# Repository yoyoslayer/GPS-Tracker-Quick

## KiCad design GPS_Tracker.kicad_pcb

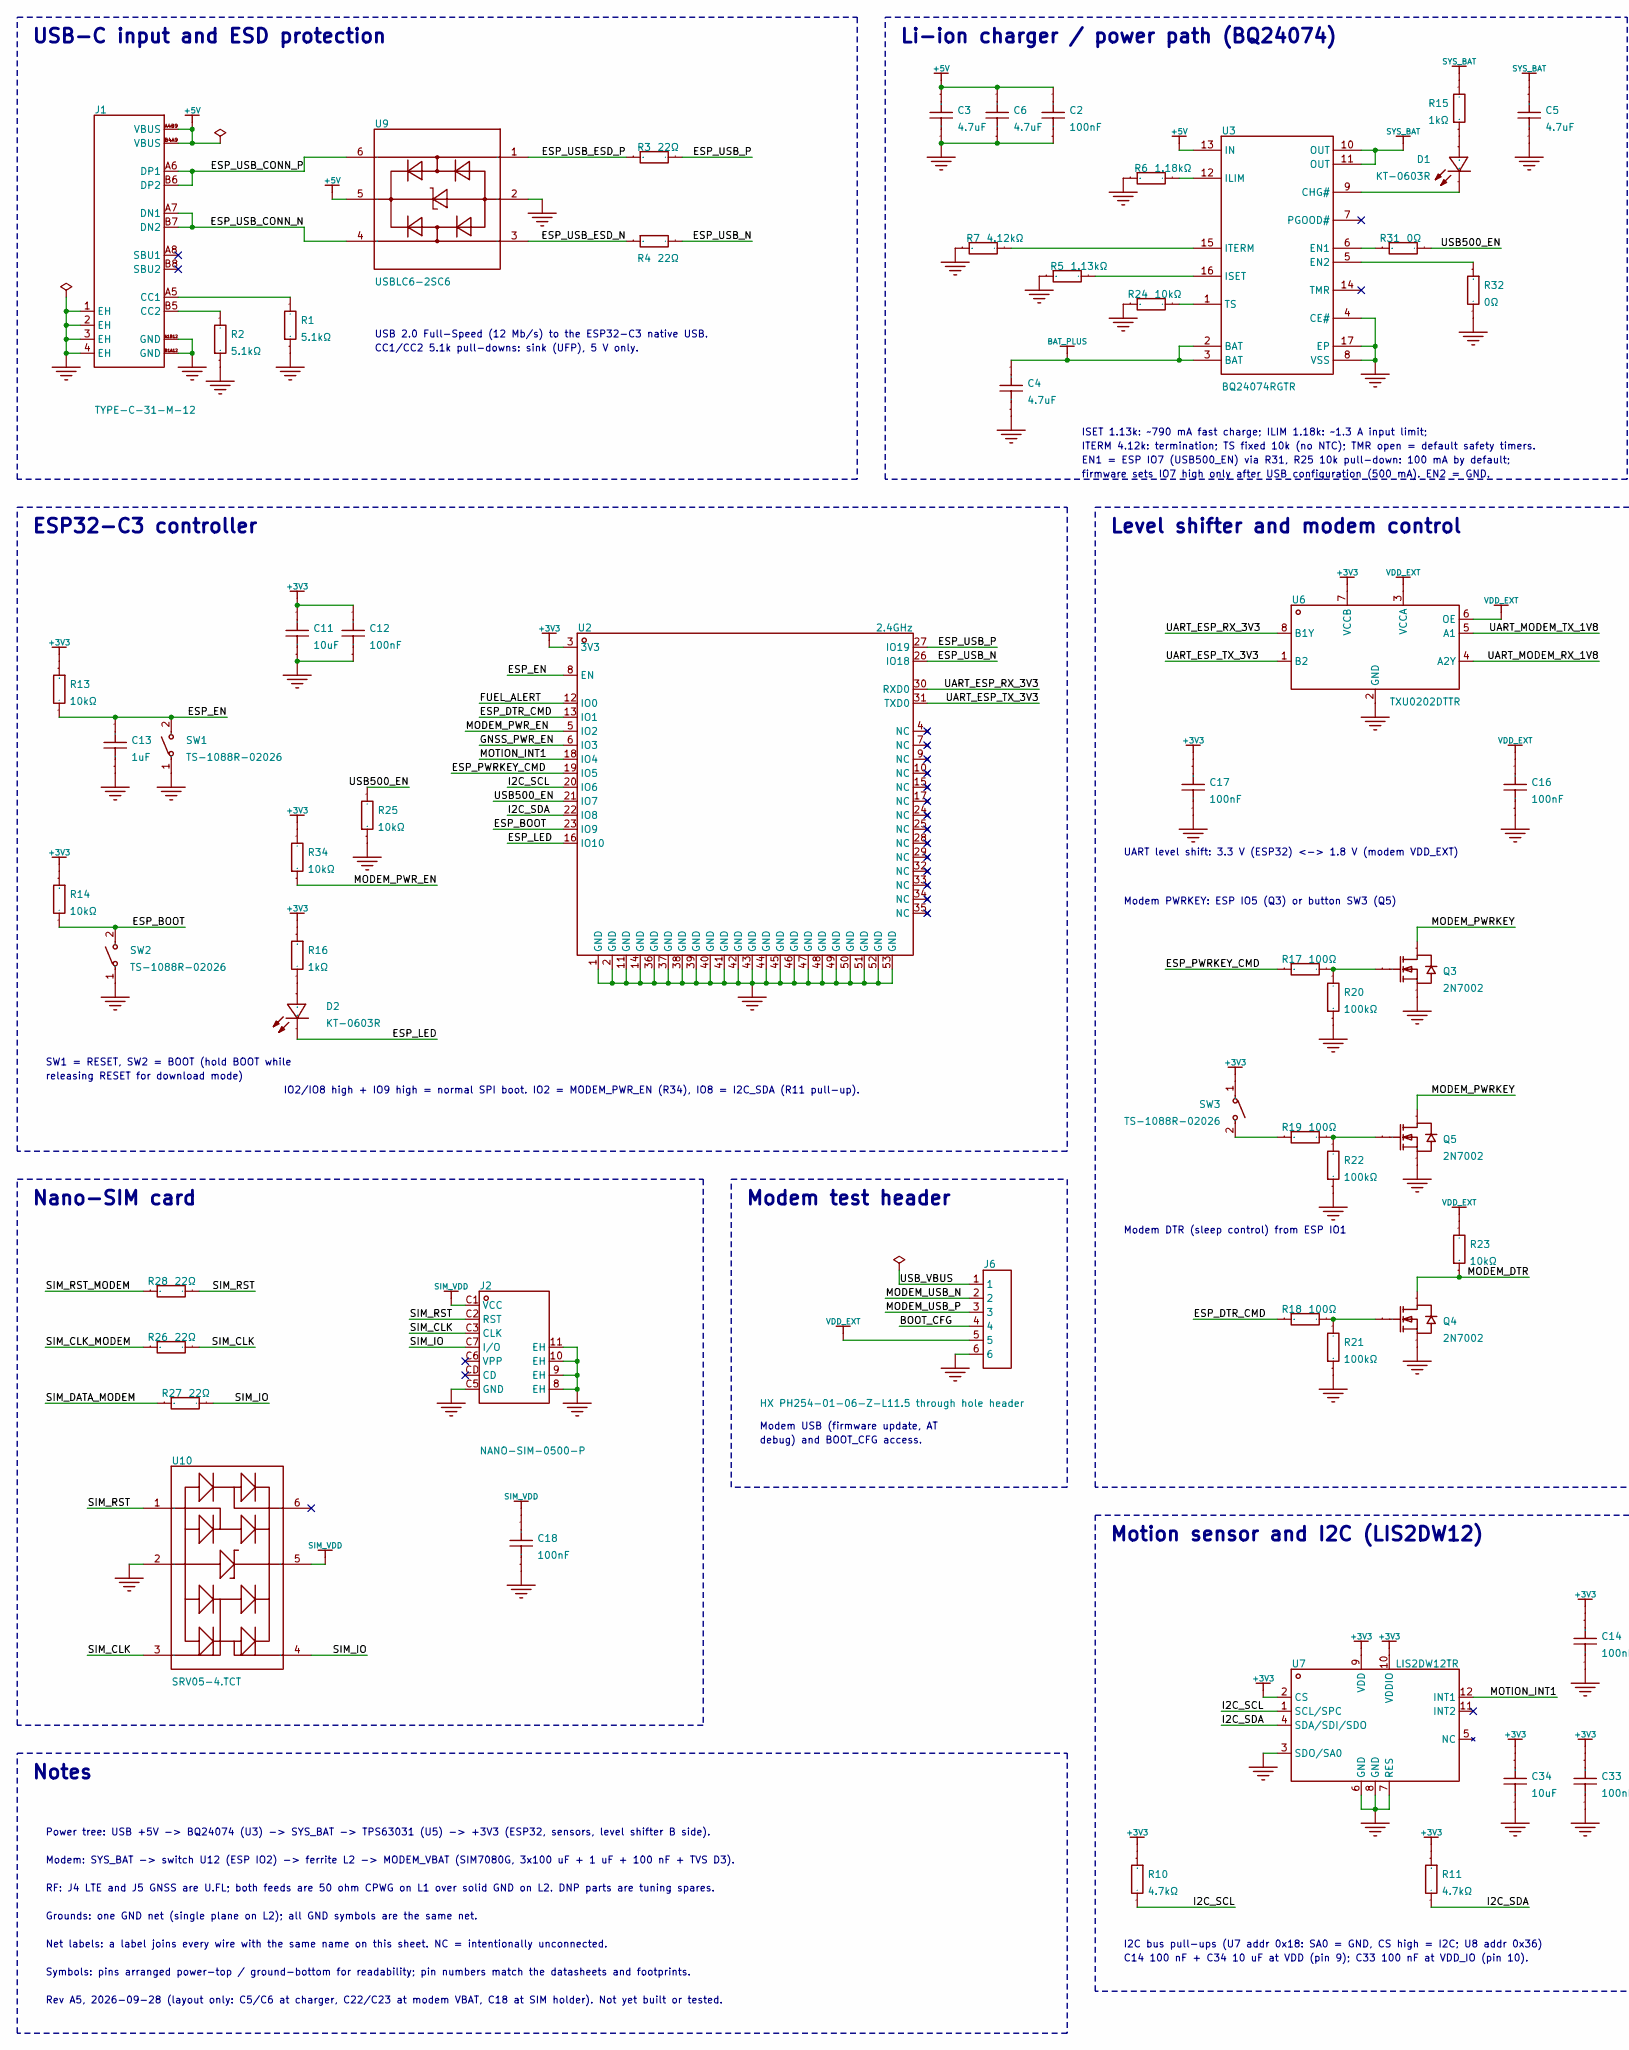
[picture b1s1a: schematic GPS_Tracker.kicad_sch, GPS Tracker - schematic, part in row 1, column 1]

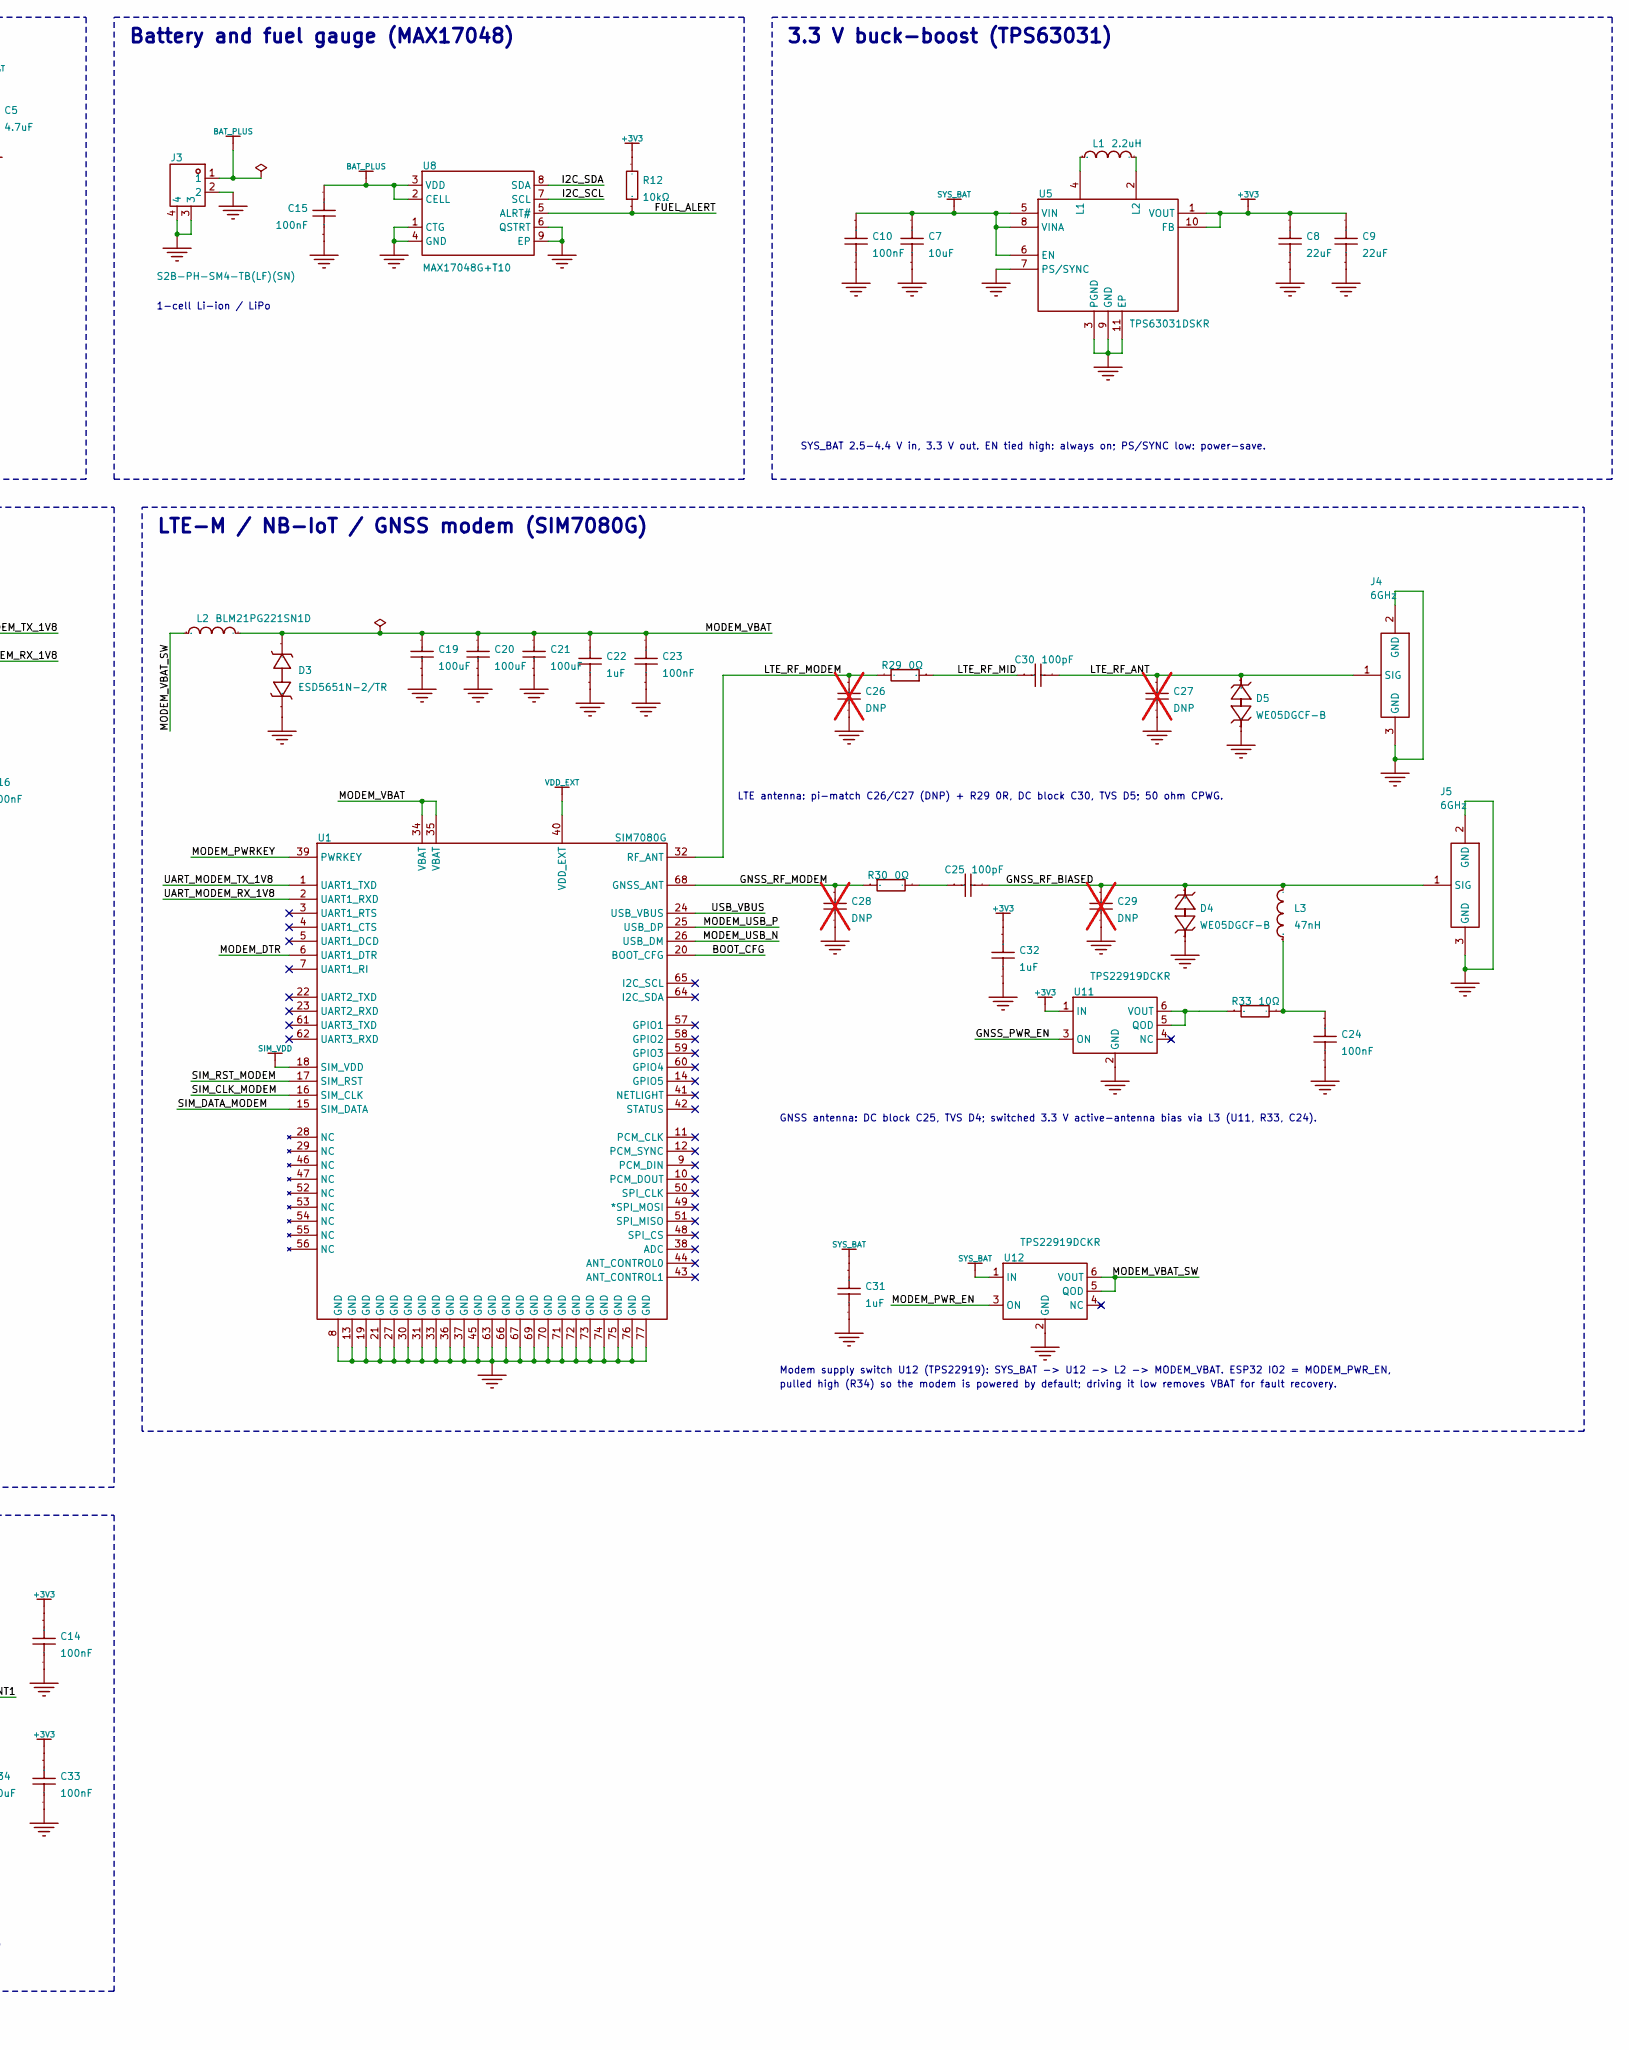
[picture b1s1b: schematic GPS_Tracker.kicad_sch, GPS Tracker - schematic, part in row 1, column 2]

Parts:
C2: 100nF; C2_C_0603_1608Metric; Manufacturer Part CC0603KRX7R9BB104; LCSC Part Name 100nF ±10% 50V
C3: 4.7uF; C3_C_0603_1608Metric; Manufacturer Part CL10A475KO8NNNC; LCSC Part Name 4.7uF ±10% 16V
C4: 4.7uF; C4_C_0603_1608Metric; Manufacturer Part CL10A475KO8NNNC; LCSC Part Name 4.7uF ±10% 16V
C5: 4.7uF; C5_C_0603_1608Metric; Manufacturer Part CL10A475KO8NNNC; LCSC Part Name 4.7uF ±10% 16V
C6: 4.7uF; C6_C_0603_1608Metric; Manufacturer Part CL10A475KO8NNNC; LCSC Part Name 4.7uF ±10% 16V
C7: 10uF; C7_C_0805_2012Metric; Manufacturer Part CL21A106KAYNNNE; LCSC Part Name 10uF ±10% 25V
C8: 22uF; C8_C_0805_2012Metric; Manufacturer Part CL21A226MAQNNNE; LCSC Part Name 22uF ±20% 25V
C9: 22uF; C9_C_0805_2012Metric; Manufacturer Part CL21A226MAQNNNE; LCSC Part Name 22uF ±20% 25V
C10: 100nF; C10_C_0603_1608Metric; Manufacturer Part CC0603KRX7R9BB104; LCSC Part Name 100nF ±10% 50V
C11: 10uF; C11_C_0805_2012Metric; Manufacturer Part CL21A106KAYNNNE; LCSC Part Name 10uF ±10% 25V
C12: 100nF; C12_C_0603_1608Metric; Manufacturer Part CC0603KRX7R9BB104; LCSC Part Name 100nF ±10% 50V
C13: 1uF; C13_C_0603_1608Metric; Manufacturer Part CL10A105KB8NNNC; LCSC Part Name 1uF ±10% 50V
C14: 100nF; C14_C_0603_1608Metric; Manufacturer Part CC0603KRX7R9BB104; LCSC Part Name 100nF ±10% 50V
C15: 100nF; C15_C_0603_1608Metric; Manufacturer Part CC0603KRX7R9BB104; LCSC Part Name 100nF ±10% 50V
C16: 100nF; C16_C_0603_1608Metric; Manufacturer Part CC0603KRX7R9BB104; LCSC Part Name 100nF ±10% 50V
C17: 100nF; C17_C_0603_1608Metric; Manufacturer Part CC0603KRX7R9BB104; LCSC Part Name 100nF ±10% 50V
C18: 100nF; C18_C_0603_1608Metric; Manufacturer Part CC0603KRX7R9BB104; LCSC Part Name 100nF ±10% 50V
C19: 100uF; C19_C_1210_3225Metric; Manufacturer Part CL32A107MQVNNNE; LCSC Part Name 100uF ±20% 6.3V
C20: 100uF; C20_C_1210_3225Metric; Manufacturer Part CL32A107MQVNNNE; LCSC Part Name 100uF ±20% 6.3V
C21: 100uF; C21_C_1210_3225Metric; Manufacturer Part CL32A107MQVNNNE; LCSC Part Name 100uF ±20% 6.3V
C22: 1uF; C22_C_0603_1608Metric; Manufacturer Part CL10A105KB8NNNC; LCSC Part Name 1uF ±10% 50V
C23: 100nF; C23_C_0603_1608Metric; Manufacturer Part CC0603KRX7R9BB104; LCSC Part Name 100nF ±10% 50V
C24: 100nF; C24_C_0603_1608Metric; Manufacturer Part CC0603KRX7R9BB104; LCSC Part Name 100nF ±10% 50V
C25, C30: 100pF; C25_C_0402_1005Metric; Manufacturer Part CL05C101JB5NNNC; LCSC Part Name 100pF ±5% 50V
C26, C27, C28, C29: DNP; C25_C_0402_1005Metric; Manufacturer Part CL05C101JB5NNNC; LCSC Part Name 100pF ±5% 50V; not fitted
C31: 1uF; C31_C_0603_1608Metric; Manufacturer Part CL10A105KB8NNNC; LCSC Part Name 1uF ±10% 50V
C32: 1uF; C32_C_0603_1608Metric; Manufacturer Part CL10A105KB8NNNC; LCSC Part Name 1uF ±10% 50V
C33: 100nF; C33_C_0603_1608Metric; Manufacturer Part CC0603KRX7R9BB104; LCSC Part Name 100nF ±10% 50V
C34: 10uF; C34_C_0805_2012Metric; Manufacturer Part CL21A106KAYNNNE; LCSC Part Name 10uF ±10% 25V
D1: KT-0603R; D1_LED_0603_1608Metric; Manufacturer Part KT-0603R; LCSC Part Name 0603 红灯 高亮
D2: KT-0603R; D2_LED_0603_1608Metric; Manufacturer Part KT-0603R; LCSC Part Name 0603 红灯 高亮
D3: ESD5651N-2/TR; D3_D_SOD-882; Manufacturer Part ESD5651N-2/TR; LCSC Part Name 双向TVS 4.5V截止 峰值脉冲电流：35A@8/20us
D4, D5: WE05DGCF-B; D4_D_SOD-882; Manufacturer Part WE05DGCF-B; LCSC Part Name 瞬态电压抑制器
J1: TYPE-C-31-M-12; J1_USB_C_Receptacle_HRO_TYPE-C-31-M-12_trimmed; Manufacturer Part TYPE-C-31-M-12; LCSC Part Name Type-C 母 卧贴
J2: NANO-SIM-0500-P; Zhongdi_NANO-SIM-0500-P; Manufacturer Part NANO-SIM-0500-P; LCSC Part Name 自弹式 NanoSIM卡 卡座
J3: S2B-PH-SM4-TB(LF)(SN); J3_JST_PH_S2B-PH-SM4-TB_1x02-1MP_P2.00mm_Horizontal_trimmed; Manufacturer Part S2B-PH-SM4-TB(LF)(SN); LCSC Part Name 1x2P 间距:2mm 卧贴 系列:PH
J4: 6GHz; J4_U.FL_Hirose_U.FL-R-SMT-1_Vertical; Manufacturer Part U.FL-R-SMT-1(80); LCSC Part Name IPEX 内针
J5: 6GHz; J5_U.FL_Hirose_U.FL-R-SMT-1_Vertical; Manufacturer Part U.FL-R-SMT-1(80); LCSC Part Name IPEX 内针
J6: HX PH254-01-06-Z-L11.5 through hole header; J6_PinHeader_1x06_P2.54mm_Vertical; Manufacturer Part HX PH254-01-06-Z-L11.5 through hole hea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; LCSC Part Name 1x6P 间距:2.54mm 方针 直插
L1: 2.2uH; L1_IND-SMD_L3.0-W3.0; Manufacturer Part SWPA3015S2R2MT; LCSC Part Name 2.2uH ±20%
L2: BLM21PG221SN1D; L2_L_0805_2012Metric; Manufacturer Part BLM21PG221SN1D; LCSC Part Name 单路 0805磁珠 阻抗220Ω@100MHz
L3: 47nH; L3_L_0402_1005Metric; Manufacturer Part SDWL1005C47NGSTF; LCSC Part Name 停产 47nH ±2%
Q3: 2N7002; Q3_SOT-23; Manufacturer Part 2N7002; LCSC Part Name 1个N沟道 耐压:60V 电流:115mA
Q4: 2N7002; Q4_SOT-23; Manufacturer Part 2N7002; LCSC Part Name 1个N沟道 耐压:60V 电流:115mA
Q5: 2N7002; Q5_SOT-23; Manufacturer Part 2N7002; LCSC Part Name 1个N沟道 耐压:60V 电流:115mA
R1: 5.1kΩ; R1_R_0603_1608Metric; Manufacturer Part 0603WAF5101T5E; LCSC Part Name 5.1kΩ ±1% 100mW 厚膜电阻
R2: 5.1kΩ; R2_R_0603_1608Metric; Manufacturer Part 0603WAF5101T5E; LCSC Part Name 5.1kΩ ±1% 100mW 厚膜电阻
R3: 22Ω; R3_R_0603_1608Metric; Manufacturer Part 0603WAF220JT5E; LCSC Part Name 22Ω ±1% 100mW 厚膜电阻
R4: 22Ω; R4_R_0603_1608Metric; Manufacturer Part 0603WAF220JT5E; LCSC Part Name 22Ω ±1% 100mW 厚膜电阻
R5: 1.13kΩ; R5_R_0603_1608Metric; Manufacturer Part 0603WAF1131T5E; LCSC Part Name 1.13kΩ ±1% 100mW 厚膜电阻
R6: 1.18kΩ; R6_R_0603_1608Metric; Manufacturer Part 0603WAF1181T5E; LCSC Part Name 1.18kΩ ±1% 100mW 厚膜电阻
R7: 4.12kΩ; R7_R_0603_1608Metric; Manufacturer Part 0603WAF4121T5E; LCSC Part Name 4.12kΩ ±1% 100mW 厚膜电阻
R10: 4.7kΩ; R10_R_0603_1608Metric; Manufacturer Part 0603WAF4701T5E; LCSC Part Name 4.7kΩ ±1% 100mW 厚膜电阻
R11: 4.7kΩ; R11_R_0603_1608Metric; Manufacturer Part 0603WAF4701T5E; LCSC Part Name 4.7kΩ ±1% 100mW 厚膜电阻
R12: 10kΩ; R12_R_0603_1608Metric; Manufacturer Part 0603WAF1002T5E; LCSC Part Name 厚膜电阻 10kΩ ±1% 100mW
R13: 10kΩ; R13_R_0603_1608Metric; Manufacturer Part 0603WAF1002T5E; LCSC Part Name 厚膜电阻 10kΩ ±1% 100mW
R14: 10kΩ; R14_R_0603_1608Metric; Manufacturer Part 0603WAF1002T5E; LCSC Part Name 厚膜电阻 10kΩ ±1% 100mW
R15: 1kΩ; R15_R_0603_1608Metric; Manufacturer Part 0603WAF1001T5E; LCSC Part Name 1kΩ ±1% 100mW 厚膜电阻
R16: 1kΩ; R16_R_0603_1608Metric; Manufacturer Part 0603WAF1001T5E; LCSC Part Name 1kΩ ±1% 100mW 厚膜电阻
R17: 100Ω; R17_R_0603_1608Metric; Manufacturer Part 0603WAF1000T5E; LCSC Part Name 100Ω ±1% 100mW 厚膜电阻
R18: 100Ω; R18_R_0603_1608Metric; Manufacturer Part 0603WAF1000T5E; LCSC Part Name 100Ω ±1% 100mW 厚膜电阻
R19: 100Ω; R19_R_0603_1608Metric; Manufacturer Part 0603WAF1000T5E; LCSC Part Name 100Ω ±1% 100mW 厚膜电阻
R20: 100kΩ; R20_R_0603_1608Metric; Manufacturer Part 0603WAF1003T5E; LCSC Part Name 100kΩ ±1% 100mW 厚膜电阻
R21: 100kΩ; R21_R_0603_1608Metric; Manufacturer Part 0603WAF1003T5E; LCSC Part Name 100kΩ ±1% 100mW 厚膜电阻
R22: 100kΩ; R22_R_0603_1608Metric; Manufacturer Part 0603WAF1003T5E; LCSC Part Name 100kΩ ±1% 100mW 厚膜电阻
R23: 10kΩ; R23_R_0603_1608Metric; Manufacturer Part 0603WAF1002T5E; LCSC Part Name 厚膜电阻 10kΩ ±1% 100mW
R24: 10kΩ; R24_R_0603_1608Metric; Manufacturer Part 0603WAF1002T5E; LCSC Part Name 厚膜电阻 10kΩ ±1% 100mW
R25: 10kΩ; R25_R_0603_1608Metric; Manufacturer Part RC0603FR-0710KL; LCSC Part Name 厚膜电阻 10kΩ ±1% 100mW
R26: 22Ω; R26_R_0603_1608Metric; Manufacturer Part 0603WAF220JT5E; LCSC Part Name 22Ω ±1% 100mW 厚膜电阻
R27: 22Ω; R27_R_0603_1608Metric; Manufacturer Part 0603WAF220JT5E; LCSC Part Name 22Ω ±1% 100mW 厚膜电阻
R28: 22Ω; R28_R_0603_1608Metric; Manufacturer Part 0603WAF220JT5E; LCSC Part Name 22Ω ±1% 100mW 厚膜电阻
R29: 0Ω; R29_R_0402_1005Metric; Manufacturer Part 0402WGF0000TCE; LCSC Part Name 0Ω ±1% 62.5mW 厚膜电阻
R30: 0Ω; R30_R_0402_1005Metric; Manufacturer Part 0402WGF0000TCE; LCSC Part Name 0Ω ±1% 62.5mW 厚膜电阻
R31: 0Ω; R31_R_0603_1608Metric; Manufacturer Part 0603WAF0000T5E; LCSC Part Name 0Ω ±1% 100mW 厚膜电阻
R32: 0Ω; R32_R_0603_1608Metric; Manufacturer Part 0603WAF0000T5E; LCSC Part Name 0Ω ±1% 100mW 厚膜电阻
R33: 10Ω; R33_R_0603_1608Metric; Manufacturer Part RC0603FR-0710RL; LCSC Part Name 厚膜电阻 10Ω ±1% 100mW
R34: 10kΩ; R34_R_0603_1608Metric; Manufacturer Part 0603WAF1002T5E; LCSC Part Name 厚膜电阻 10kΩ ±1% 100mW
SW1: TS-1088R-02026; SW1_SW_Push_1P1T_NO_CK_KMR2; Manufacturer Part TS-1088R-02026; LCSC Part Name 3.9*2.93*2mm 立贴 轻触开关
SW2: TS-1088R-02026; SW2_SW_Push_1P1T_NO_CK_KMR2; Manufacturer Part TS-1088R-02026; LCSC Part Name 3.9*2.93*2mm 立贴 轻触开关
SW3: TS-1088R-02026; SW3_SW_Push_1P1T_NO_CK_KMR2; Manufacturer Part TS-1088R-02026; LCSC Part Name 3.9*2.93*2mm 立贴 轻触开关
U1: SIM7080G; SIMCom_SIM7080G_HD_V1.03; Manufacturer Part SIM7080G; LCSC Part Name 多频段CAT-M和NB-IoT模块
U2: 2.4GHz; U2_ESP32-C3-MINI-1_trimmed; Manufacturer Part ESP32-C3-MINI-1-H4X; LCSC Part Name 不带固件 支持2.4GHz Wi-Fi和蓝牙5的小尺寸模组
U3: BQ24074RGTR; U3_QFN-16-1EP_3x3mm_P0.5mm_EP1.7x1.7mm; Manufacturer Part BQ24074RGTR; LCSC Part Name 1.5A USB友好型锂离子电池充电器和电源路径管理IC
U5: TPS63031DSKR; U5_WSON-10-1EP_2.5x2.5mm_P0.5mm_EP1.2x2mm; Manufacturer Part TPS63031DSKR; LCSC Part Name 升降压型 900mA 1.8V~5.5V
U6: TXU0202DTTR; U6_Texas_X1SON-8_2x1mm_P0.5mm; Manufacturer Part TXU0202DTTR; LCSC Part Name 具有施密特触发输入和三态输出的双位定向电压电平转换器
U7: LIS2DW12TR; U7_LGA-12_2x2mm_P0.5mm; Manufacturer Part LIS2DW12TR; LCSC Part Name 高性能超低功耗3轴加速度计
U8: MAX17048G+T10; U8_TDFN-8-1EP_2x2mm_P0.5mm_EP0.8x1.2mm; Manufacturer Part MAX17048G+T10; LCSC Part Name 3uA单节/双节电池电量计，带ModelGauge算法
U9: USBLC6-2SC6; U9_SOT-23-6; Manufacturer Part USBLC6-2SC6; LCSC Part Name 单向ESD
U10: SRV05-4.TCT; U10_SOT-23-6; Manufacturer Part SRV05-4.TCT; LCSC Part Name SRV05-4.TCT
U11: TPS22919DCKR; U11_SOT-363_SC-70-6; Manufacturer Part TPS22919DCKR; LCSC Part Name 具有受控上升时间的5.5V、1.5A、90mΩ自保护负载开关
U12: TPS22919DCKR; U12_SOT-363_SC-70-6; Manufacturer Part TPS22919DCKR; LCSC Part Name 具有受控上升时间的5.5V、1.5A、90mΩ自保护负载开关

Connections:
+3V3: C8.2, C9.2, C11.2, C12.2, C14.1, C17.1, C32.1, C33.1, C34.1, R10.1, R11.1, R12.2, R13.1, R14.1, R16.1, R34.2, SW3.1, U2.3 (3V3), U5.1 (VOUT), U5.10 (FB), U6.7 (VCCB), U7.2 (CS), U7.9 (VDD), U7.10 (VDDIO), U11.1 (IN); also elsewhere on the board
+5V: C2.2, C3.1, C6.2, J1.A4B9 (VBUS), J1.B4A9 (VBUS), U3.13 (IN), U9.5
/BOOT_CFG: J6.4, U1.20 (BOOT_CFG)
/ESP_BOOT: R14.2, SW2.2, U2.23 (IO9)
/ESP_DTR_CMD: R18.1, U2.13 (IO1)
/ESP_EN: C13.2, R13.2, SW1.2, U2.8 (EN)
/ESP_LED: D2.2 (K), U2.16 (IO10)
/ESP_PWRKEY_CMD: R17.1, U2.19 (IO5)
/ESP_USB_CONN_N: J1.A7 (DN1), J1.B7 (DN2), U9.4
/ESP_USB_CONN_P: J1.A6 (DP1), J1.B6 (DP2), U9.6
/ESP_USB_ESD_N: R4.1, U9.3
/ESP_USB_ESD_P: R3.1, U9.1
/ESP_USB_N: R4.2, U2.26 (IO18)
/ESP_USB_P: R3.2, U2.27 (IO19)
/FUEL_ALERT: R12.1, U2.12 (IO0), U8.5 (ALRT#)
/GNSS_PWR_EN: U2.6 (IO3), U11.3 (ON)
/GNSS_RF_BIASED: C25.2, C29.1, D4.1, J5.1 (SIG), L3.2
/GNSS_RF_MODEM: C28.1, R30.1, U1.68 (GNSS_ANT)
/I2C_SCL: R10.2, U2.20 (IO6), U7.1 (SCL/SPC), U8.7 (SCL); also elsewhere on the board
/I2C_SDA: R11.2, U2.22 (IO8), U7.4 (SDA/SDI/SDO), U8.8 (SDA); also elsewhere on the board
/LTE_RF_ANT: C27.1, C30.2, D5.1, J4.1 (SIG)
/LTE_RF_MID: C30.1, R29.1
/LTE_RF_MODEM: C26.1, R29.2, U1.32 (RF_ANT)
/MODEM_DTR: Q4.3 (D), R23.1, U1.6 (UART1_DTR)
/MODEM_PWRKEY: Q3.3 (D), Q5.3 (D), U1.39 (PWRKEY); also elsewhere on the board
/MODEM_PWR_EN: R34.1, U2.5 (IO2), U12.3 (ON)
/MODEM_USB_N: J6.2, U1.26 (USB_DM)
/MODEM_USB_P: J6.3, U1.25 (USB_DP)
/MODEM_VBAT: C19.2, C20.2, C21.2, C22.2, C23.2, D3.2, L2.2, U1.34 (VBAT), U1.35 (VBAT)
/MODEM_VBAT_SW: L2.1, U12.5 (QOD), U12.6 (VOUT)
/MOTION_INT1: U2.18 (IO4), U7.12 (INT1)
/SIM_CLK: J2.C3 (CLK), R26.2, U10.3
/SIM_CLK_MODEM: R26.1, U1.16 (SIM_CLK)
/SIM_DATA_MODEM: R27.1, U1.15 (SIM_DATA)
/SIM_IO: J2.C7 (I/O), R27.2, U10.4
/SIM_RST: J2.C2 (RST), R28.2, U10.1
/SIM_RST_MODEM: R28.1, U1.17 (SIM_RST)
/UART_ESP_RX_3V3: U2.30 (RXD0), U6.8 (B1Y)
/UART_ESP_TX_3V3: U2.31 (TXD0), U6.1 (B2)
/UART_MODEM_RX_1V8: U1.2 (UART1_RXD), U6.4 (A2Y)
/UART_MODEM_TX_1V8: U1.1 (UART1_TXD), U6.5 (A1)
/USB500_EN: R25.2, R31.2, U2.21 (IO7)
/USB_VBUS: J6.1, U1.24 (USB_VBUS)
BAT_PLUS: C4.2, C15.2, J3.1, U3.2 (BAT), U3.3 (BAT), U8.2 (CELL), U8.3 (VDD); also elsewhere on the board
GND: C2.1, C3.2, C4.1, C5.2, C6.1, C7.1, C8.1, C9.1, C10.2, C11.1, C12.1, C13.1, C14.2, C15.1, C16.1, C17.2, C18.1, C19.1, C20.1, C21.1, C22.1, C23.1, C24.2, C26.2, C27.2, C28.2, C29.2, C31.2, C32.2, C33.2, C34.2, D3.1, D4.2, D5.2, J1.1 (EH), J1.2 (EH), J1.3 (EH), J1.4 (EH), J1.A1B12 (GND), J1.B1A12 (GND), J2.8 (EH), J2.9 (EH), J2.10 (EH), J2.11 (EH), J2.C5 (GND), J3.2, J3.3, J3.4, J4.2 (GND), J4.3 (GND), J5.2 (GND), J5.3 (GND), J6.6, Q3.2 (S), Q4.2 (S), Q5.2 (S), R1.1, R2.1, R5.1, R6.1, R7.1, R20.1, R21.1, R22.1, R24.1, R25.1, R32.2, SW1.1, SW2.1, U1.8 (GND), U1.13 (GND), U1.19 (GND), U1.21 (GND), U1.27 (GND), U1.30 (GND), U1.31 (GND), U1.33 (GND), U1.36 (GND), U1.37 (GND), U1.45 (GND), U1.63 (GND), U1.66 (GND), U1.67 (GND), U1.69 (GND), U1.70 (GND), U1.71 (GND), U1.72 (GND), U1.73 (GND), U1.74 (GND), U1.75 (GND), U1.76 (GND), U1.77 (GND), U2.1 (GND), U2.2 (GND), U2.11 (GND), U2.14 (GND), U2.36 (GND), U2.37 (GND), U2.38 (GND), U2.39 (GND), U2.40 (GND), U2.41 (GND), U2.42 (GND), U2.43 (GND), U2.44 (GND), U2.45 (GND), U2.46 (GND), U2.47 (GND), U2.48 (GND), U2.49 (GND), U2.50 (GND), U2.51 (GND), U2.52 (GND), U2.53 (GND), U3.4 (CE#), U3.8 (VSS), U3.17 (EP), U5.3 (PGND), U5.7 (PS/SYNC), U5.9 (GND), U5.11 (EP), U6.2 (GND), U7.3 (SDO/SA0), U7.6 (GND), U7.7 (RES), U7.8 (GND), U8.1 (CTG), U8.4 (GND), U8.6 (QSTRT), U8.9 (EP), U9.2, U10.2, U11.2 (GND), U12.2 (GND)
unnamed: C24.1, L3.1, R33.2
unnamed: C25.1, R30.2
unnamed: D1.1 (A), R15.1
unnamed: D1.2 (K), U3.9 (CHG#)
unnamed: D2.1 (A), R16.2
unnamed: J1.A5 (CC1), R1.2
unnamed: J1.B5 (CC2), R2.2
unnamed: Q3.1 (G), R17.2, R20.2
unnamed: Q4.1 (G), R18.2, R21.2
unnamed: Q5.1 (G), R19.2, R22.2
unnamed: R19.1, SW3.2
unnamed: R31.1, U3.6 (EN1)
unnamed: R32.1, U3.5 (EN2)
unnamed: R6.2, U3.12 (ILIM)
unnamed: R5.2, U3.16 (ISET)
unnamed: R7.2, U3.15 (ITERM)
unnamed: R24.2, U3.1 (TS)
unnamed: L1.1, U5.4 (L1)
unnamed: L1.2, U5.2 (L2)
unnamed: R33.1, U11.5 (QOD), U11.6 (VOUT)
SIM_VDD: C18.2, J2.C1 (VCC), U1.18 (SIM_VDD), U10.5
SYS_BAT: C5.1, C7.2, C10.1, C31.1, R15.2, U3.10 (OUT), U3.11 (OUT), U5.5 (VIN), U5.6 (EN), U5.8 (VINA), U12.1 (IN); also elsewhere on the board
VDD_EXT: C16.2, J6.5, R23.2, U1.40 (VDD_EXT), U6.3 (VCCA), U6.6 (OE); also elsewhere on the board

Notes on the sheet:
USB-C input and ESD protection
USB 2.0 Full-Speed (12 Mb/s) to the ESP32-C3 native USB.
CC1/CC2 5.1k pull-downs: sink (UFP), 5 V only.
Li-ion charger / power path (BQ24074)
ISET 1.13k: ~790 mA fast charge; ILIM 1.18k: ~1.3 A input limit;
ITERM 4.12k: termination; TS fixed 10k (no NTC); TMR open = default safety timers.
1-cell Li-ion / LiPo
Battery and fuel gauge (MAX17048)
3.3 V buck-boost (TPS63031)
SYS_BAT 2.5-4.4 V in, 3.3 V out. EN tied high: always on; PS/SYNC low: power-save.
SW1 = RESET, SW2 = BOOT (hold BOOT while
releasing RESET for download mode)
IO2/IO8 high + IO9 high = normal SPI boot. IO2 = MODEM_PWR_EN (R34), IO8 = I2C_SDA (R11 pull-up).
ESP32-C3 controller
UART level shift: 3.3 V (ESP32) <-> 1.8 V (modem VDD_EXT)
Modem PWRKEY: ESP IO5 (Q3) or button SW3 (Q5)
Modem DTR (sleep control) from ESP IO1
Level shifter and modem control
LTE antenna: pi-match C26/C27 (DNP) + R29 0R, DC block C30, TVS D5; 50 ohm CPWG.
GNSS antenna: DC block C25, TVS D4; switched 3.3 V active-antenna bias via L3 (U11, R33, C24).
LTE-M / NB-IoT / GNSS modem (SIM7080G)
Nano-SIM card
Modem test header
Modem USB (firmware update, AT
debug) and BOOT_CFG access.
I2C bus pull-ups (U7 addr 0x18: SA0 = GND, CS high = I2C; U8 addr 0x36)
Motion sensor and I2C (LIS2DW12)
Notes
Power tree: USB +5V -> BQ24074 (U3) -> SYS_BAT -> TPS63031 (U5) -> +3V3 (ESP32, sensors, level shifter B side).
Modem: SYS_BAT -> switch U12 (ESP IO2) -> ferrite L2 -> MODEM_VBAT (SIM7080G, 3x100 uF + 1 uF + 100 nF + TVS D3).
RF: J4 LTE and J5 GNSS are U.FL; both feeds are 50 ohm CPWG on L1 over solid GND on L2. DNP parts are tuning spares.
Grounds: one GND net (single plane on L2); all GND symbols are the same net.
Net labels: a label joins every wire with the same name on this sheet. NC = intentionally unconnected.
Symbols: pins arranged power-top / ground-bottom for readability; pin numbers match the datasheets and footprints.
Rev A5, 2026-09-28 (layout only: C5/C6 at charger, C22/C23 at modem VBAT, C18 at SIM holder). Not yet built or tested.
Modem supply switch U12 (TPS22919): SYS_BAT -> U12 -> L2 -> MODEM_VBAT. ESP32 IO2 = MODEM_PWR_EN,
pulled high (R34) so the modem is powered by default; driving it low removes VBAT for fault recovery.
C14 100 nF + C34 10 uF at VDD (pin 9); C33 100 nF at VDD_IO (pin 10).
EN1 = ESP IO7 (USB500_EN) via R31, R25 10k pull-down: 100 mA by default;
firmware sets IO7 high only after USB configuration (500 mA). EN2 = GND.

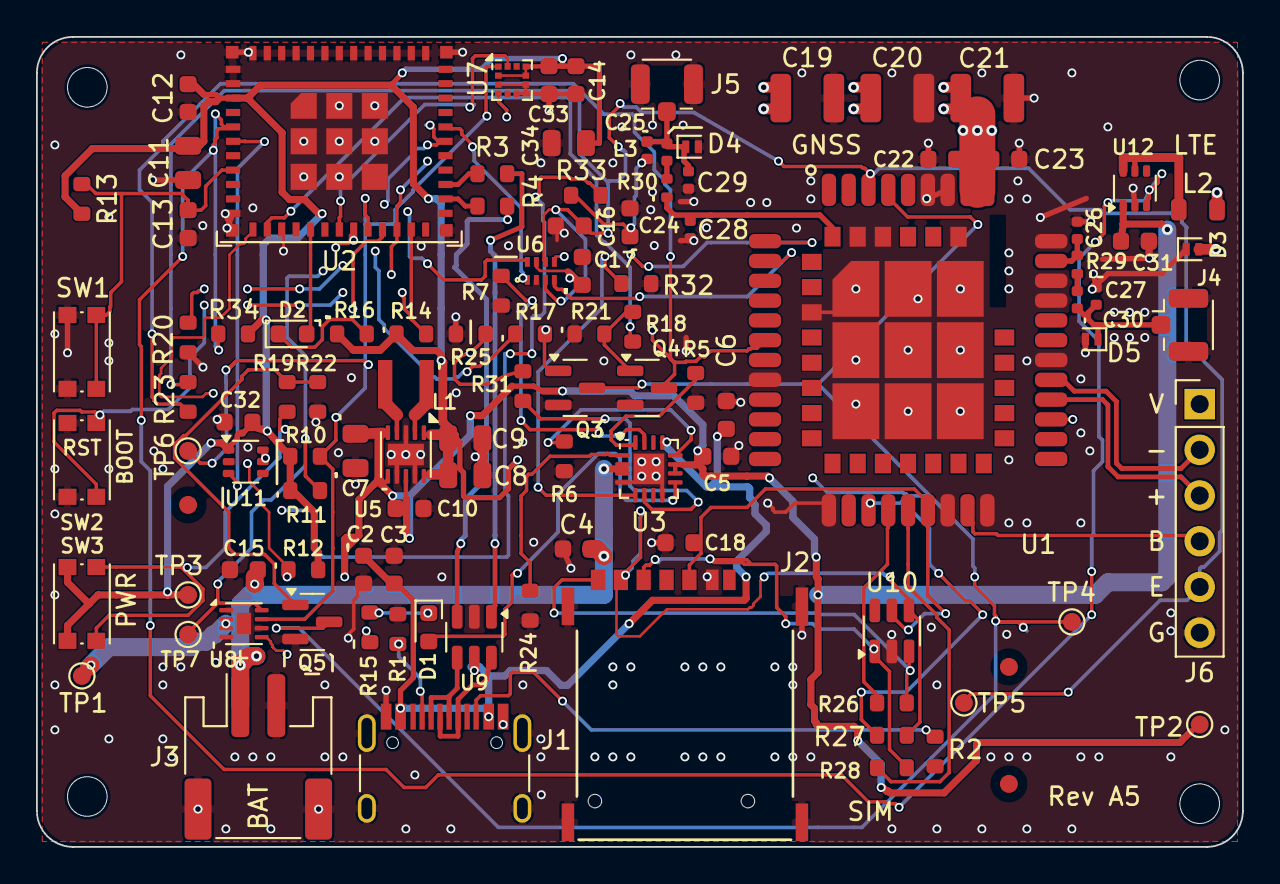
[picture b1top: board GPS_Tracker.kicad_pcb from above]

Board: 4 copper layers, 67.0 x 45.0 mm, 110 parts (0 on the bottom side), 68 nets.

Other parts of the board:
FID1, FID2, FID3: FIDUCIAL; Fiducial_1mm_Mask2mm
H1: MountingHole_2.2mm_M2; H1_MountingHole_2.2mm_M2
H2: MountingHole_2.2mm_M2; H2_MountingHole_2.2mm_M2
H3: MountingHole_2.2mm_M2; H3_MountingHole_2.2mm_M2
H4: MountingHole_2.2mm_M2; H4_MountingHole_2.2mm_M2
TP1: BAT_PLUS; TestPoint_Pad_D1.0mm
TP2: SYS_BAT; TestPoint_Pad_D1.0mm
TP3: +3V3; TestPoint_Pad_D1.0mm
TP4: PWRKEY; TestPoint_Pad_D1.0mm
TP5: VDD_EXT; TestPoint_Pad_D1.0mm
TP6: SCL; TestPoint_Pad_D1.0mm
TP7: SDA; TestPoint_Pad_D1.0mm

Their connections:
+3V3: TP3.1; also elsewhere on the board
/I2C_SCL: TP6.1; also elsewhere on the board
/I2C_SDA: TP7.1; also elsewhere on the board
/MODEM_PWRKEY: TP4.1; also elsewhere on the board
BAT_PLUS: TP1.1; also elsewhere on the board
SYS_BAT: TP2.1; also elsewhere on the board
VDD_EXT: TP5.1; also elsewhere on the board

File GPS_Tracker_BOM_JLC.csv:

"Designator","Value","Footprint","LCSC Part #","Manufacturer Part","Manufacturer","Quantity","DNP"
"C2,C10,C12,C14,C15,C16,C17,C18,C23,C24,C33","100nF","Board_Imported:C10_C_0603_1608Metric,Board_Imported:C12_C_0603_1608Metric,Board_Imported:C14_C_0603_1608Metric,Board_Imported:C15_C_0603_1608Metric,Board_Imported:C16_C_0603_1608Metric,Board_Imported:C17_C_0603_1608Metric,Board_Imported:C18_C_0603_1608Metric,Board_Imported:C23_C_0603_1608Metric,Board_Imported:C24_C_0603_1608Metric,Board_Imported:C2_C_0603_1608Metric,Board_Imported:C33_C_0603_1608Metric","C14663","CC0603KRX7R9BB104","YAGEO(国巨)","11",""
"C3,C4,C5,C6","4.7uF","Board_Imported:C3_C_0603_1608Metric,Board_Imported:C4_C_0603_1608Metric,Board_Imported:C5_C_0603_1608Metric,Board_Imported:C6_C_0603_1608Metric","C19666","CL10A475KO8NNNC","SAMSUNG(三星)","4",""
"C7,C11,C34","10uF","Board_Imported:C11_C_0805_2012Metric,Board_Imported:C34_C_0805_2012Metric,Board_Imported:C7_C_0805_2012Metric","C15850","CL21A106KAYNNNE","SAMSUNG(三星)","3",""
"C8,C9","22uF","Board_Imported:C8_C_0805_2012Metric,Board_Imported:C9_C_0805_2012Metric","C45783","CL21A226MAQNNNE","SAMSUNG(三星)","2",""
"C13,C22,C31,C32","1uF","Board_Imported:C13_C_0603_1608Metric,Board_Imported:C22_C_0603_1608Metric,Board_Imported:C31_C_0603_1608Metric,Board_Imported:C32_C_0603_1608Metric","C15849","CL10A105KB8NNNC","SAMSUNG(三星)","4",""
"C19,C20,C21","100uF","Board_Imported:C19_C_1210_3225Metric,Board_Imported:C20_C_1210_3225Metric,Board_Imported:C21_C_1210_3225Metric","C49066","CL32A107MQVNNNE","SAMSUNG(三星)","3",""
"C25,C30","100pF","Board_Imported:C25_C_0402_1005Metric","C26409","CL05C101JB5NNNC","SAMSUNG(三星)","2",""
"D1,D2","KT-0603R","Board_Imported:D1_LED_0603_1608Metric,Board_Imported:D2_LED_0603_1608Metric","C2286","KT-0603R","KENTO","2",""
"D3","ESD5651N-2/TR","Board_Imported:D3_D_SOD-882","C239784","ESD5651N-2/TR","WILLSEMI(韦尔)","1",""
"D4,D5","WE05DGCF-B","Board_Imported:D4_D_SOD-882","C3039401","WE05DGCF-B","Wayon(上海维安)","2",""
"J1","TYPE-C-31-M-12","Board_Imported:J1_USB_C_Receptacle_HRO_TYPE-C-31-M-12_trimmed","C165948","TYPE-C-31-M-12","韩国韩荣","1",""
"J2","NANO-SIM-0500-P","Validated:Zhongdi_NANO-SIM-0500-P","C29780388","NANO-SIM-0500-P","Zhongdi(众迪)","1",""
"J3","S2B-PH-SM4-TB(LF)(SN)","Board_Imported:J3_JST_PH_S2B-PH-SM4-TB_1x02-1MP_P2.00mm_Horizontal_trimmed","C295747","S2B-PH-SM4-TB(LF)(SN)","JST","1",""
"J4,J5","6GHz","Board_Imported:J4_U.FL_Hirose_U.FL-R-SMT-1_Vertical,Board_Imported:J5_U.FL_Hirose_U.FL-R-SMT-1_Vertical","C88374","U.FL-R-SMT-1(80)","HRS(广濑)","2",""
"J6","HX PH254-01-06-Z-L11.5 through hole header","Board_Imported:J6_PinHeader_1x06_P2.54mm_Vertical","C52016393","HX PH254-01-06-Z-L11.5 through hole header","hanxia(韩下)","1",""
"L1","2.2uH","EasyEDA_Source:L1_IND-SMD_L3.0-W3.0","C43389","SWPA3015S2R2MT","Sunlord(顺络)","1",""
"L2","BLM21PG221SN1D","Board_Imported:L2_L_0805_2012Metric","C85840","BLM21PG221SN1D","muRata(村田)","1",""
"L3","47nH","Board_Imported:L3_L_0402_1005Metric","C95948","SDWL1005C47NGSTF","Sunlord(顺络)","1",""
"Q3,Q4,Q5","2N7002","Board_Imported:Q3_SOT-23,Board_Imported:Q4_SOT-23,Board_Imported:Q5_SOT-23","C8545","2N7002","CJ(江苏长电/长晶)","3",""
"R1,R2","5.1kΩ","Board_Imported:R1_R_0603_1608Metric,Board_Imported:R2_R_0603_1608Metric","C23186","0603WAF5101T5E","UNI-ROYAL(厚声)","2",""
"R3,R4,R26,R27,R28","22Ω","Board_Imported:R26_R_0603_1608Metric,Board_Imported:R27_R_0603_1608Metric,Board_Imported:R28_R_0603_1608Metric,Board_Imported:R3_R_0603_1608Metric,Board_Imported:R4_R_0603_1608Metric","C23345","0603WAF220JT5E","UNI-ROYAL(厚声)","5",""
"R5","1.13kΩ","Board_Imported:R5_R_0603_1608Metric","C22833","0603WAF1131T5E","UNI-ROYAL(厚声)","1",""
"R6","1.18kΩ","Board_Imported:R6_R_0603_1608Metric","C22763","0603WAF1181T5E","UNI-ROYAL(厚声)","1",""
"R7","4.12kΩ","Board_Imported:R7_R_0603_1608Metric","C23041","0603WAF4121T5E","UNI-ROYAL(厚声)","1",""
"R10,R11","4.7kΩ","Board_Imported:R10_R_0603_1608Metric,Board_Imported:R11_R_0603_1608Metric","C23162","0603WAF4701T5E","UNI-ROYAL(厚声)","2",""
"R12,R13,R14,R23,R24,R34","10kΩ","Board_Imported:R12_R_0603_1608Metric,Board_Imported:R13_R_0603_1608Metric,Board_Imported:R14_R_0603_1608Metric,Board_Imported:R23_R_0603_1608Metric,Board_Imported:R24_R_0603_1608Metric,Board_Imported:R34_R_0603_1608Metric","C25804","0603WAF1002T5E","UNI-ROYAL(厚声)","6",""
"R15,R16","1kΩ","Board_Imported:R15_R_0603_1608Metric,Board_Imported:R16_R_0603_1608Metric","C21190","0603WAF1001T5E","UNI-ROYAL(厚声)","2",""
"R17,R18,R19","100Ω","Board_Imported:R17_R_0603_1608Metric,Board_Imported:R18_R_0603_1608Metric,Board_Imported:R19_R_0603_1608Metric","C22775","0603WAF1000T5E","UNI-ROYAL(厚声)","3",""
"R20,R21,R22","100kΩ","Board_Imported:R20_R_0603_1608Metric,Board_Imported:R21_R_0603_1608Metric,Board_Imported:R22_R_0603_1608Metric","C25803","0603WAF1003T5E","UNI-ROYAL(厚声)","3",""
"R25","10kΩ","Board_Imported:R25_R_0603_1608Metric","C98220","RC0603FR-0710KL","YAGEO(国巨)","1",""
"R29,R30","0Ω","Board_Imported:R29_R_0402_1005Metric,Board_Imported:R30_R_0402_1005Metric","C17168","0402WGF0000TCE","UNI-ROYAL(厚声)","2",""
"R31,R32","0Ω","Board_Imported:R31_R_0603_1608Metric,Board_Imported:R32_R_0603_1608Metric","C21189","0603WAF0000T5E","UNI-ROYAL(厚声)","2",""
"R33","10Ω","Board_Imported:R33_R_0603_1608Metric","C109318","RC0603FR-0710RL","YAGEO(国巨)","1",""
"SW1,SW2,SW3","TS-1088R-02026","Board_Imported:SW1_SW_Push_1P1T_NO_CK_KMR2,Board_Imported:SW2_SW_Push_1P1T_NO_CK_KMR2,Board_Imported:SW3_SW_Push_1P1T_NO_CK_KMR2","C455280","TS-1088R-02026","XUNPU(讯普)","3",""
"U1","SIM7080G","Validated:SIMCom_SIM7080G_HD_V1.03","C2943992","SIM7080G","SIMCOM(芯讯通无线科技)","1",""
"U2","2.4GHz","Board_Imported:U2_ESP32-C3-MINI-1_trimmed","C41349510","ESP32-C3-MINI-1-H4X","ESPRESSIF(乐鑫)","1",""
"U3","BQ24074RGTR","Board_Imported:U3_QFN-16-1EP_3x3mm_P0.5mm_EP1.7x1.7mm","C54313","BQ24074RGTR","TI(德州仪器)","1",""
"U5","TPS63031DSKR","Board_Imported:U5_WSON-10-1EP_2.5x2.5mm_P0.5mm_EP1.2x2mm","C15516","TPS63031DSKR","TI(德州仪器)","1",""
"U6","TXU0202DTTR","Board_Imported:U6_Texas_X1SON-8_2x1mm_P0.5mm","C18197534","TXU0202DTTR","TI(德州仪器)","1",""
"U7","LIS2DW12TR","Board_Imported:U7_LGA-12_2x2mm_P0.5mm","C189624","LIS2DW12TR","ST(意法半导体)","1",""
"U8","MAX17048G+T10","Board_Imported:U8_TDFN-8-1EP_2x2mm_P0.5mm_EP0.8x1.2mm","C2682616","MAX17048G+T10","ADI(亚德诺)/MAXIM(美信)","1",""
"U9","USBLC6-2SC6","Board_Imported:U9_SOT-23-6","C7519","USBLC6-2SC6","ST(意法半导体)","1",""
"U10","SRV05-4.TCT","Board_Imported:U10_SOT-23-6","C13612","SRV05-4.TCT","SEMTECH","1",""
"U11,U12","TPS22919DCKR","Board_Imported:U11_SOT-363_SC-70-6,Board_Imported:U12_SOT-363_SC-70-6","C2149796","TPS22919DCKR","TI(德州仪器)","2",""
